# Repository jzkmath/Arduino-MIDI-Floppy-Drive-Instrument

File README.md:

# Arduino MIDI Floppy Drive Instrument

This is the design files for an Arduino Floppy-Drive controller that is MIDI Controlled.
It is a combination of the [MIDI Stepper Synth V1](https://github.com/jzkmath/Arduino-MIDI-Stepper-Motor-Instrument) and [Moppy Software](https://github.com/SammyIAm/Moppy2).

The core method for controlling the floppy drives is the use of a non-blocking delay. If you want to make a stepper motor play at a certain frequency, simply pulse the pin at that specified frequency. In this case however, the position of the drive head is important, so we simply need to track the position and reverse direction when that point is reached.

Refer to the schematic for pinouts. The header pins connect to the IDE connector of the floppy drive and maintain the ground reference.

Look at this pinout:

We need to connect "drive select" together (Pins 11 and 12) to enable the drive and then connect the Step and Direction to the Shield. 

### PINOUT:
12 - Drive Select (Enable)

11 - Drive Select Ground

18 - Direction

17 - Direction Ground

20 - Step

19 - Step Ground

## NOTE:
There is a two pin header (J14) that is the programming jumper. The jumper should be installed here and removed when the Arduino is being programmed. This is because the MIDI Rx line is also use to program the Arduino when its being flashed.

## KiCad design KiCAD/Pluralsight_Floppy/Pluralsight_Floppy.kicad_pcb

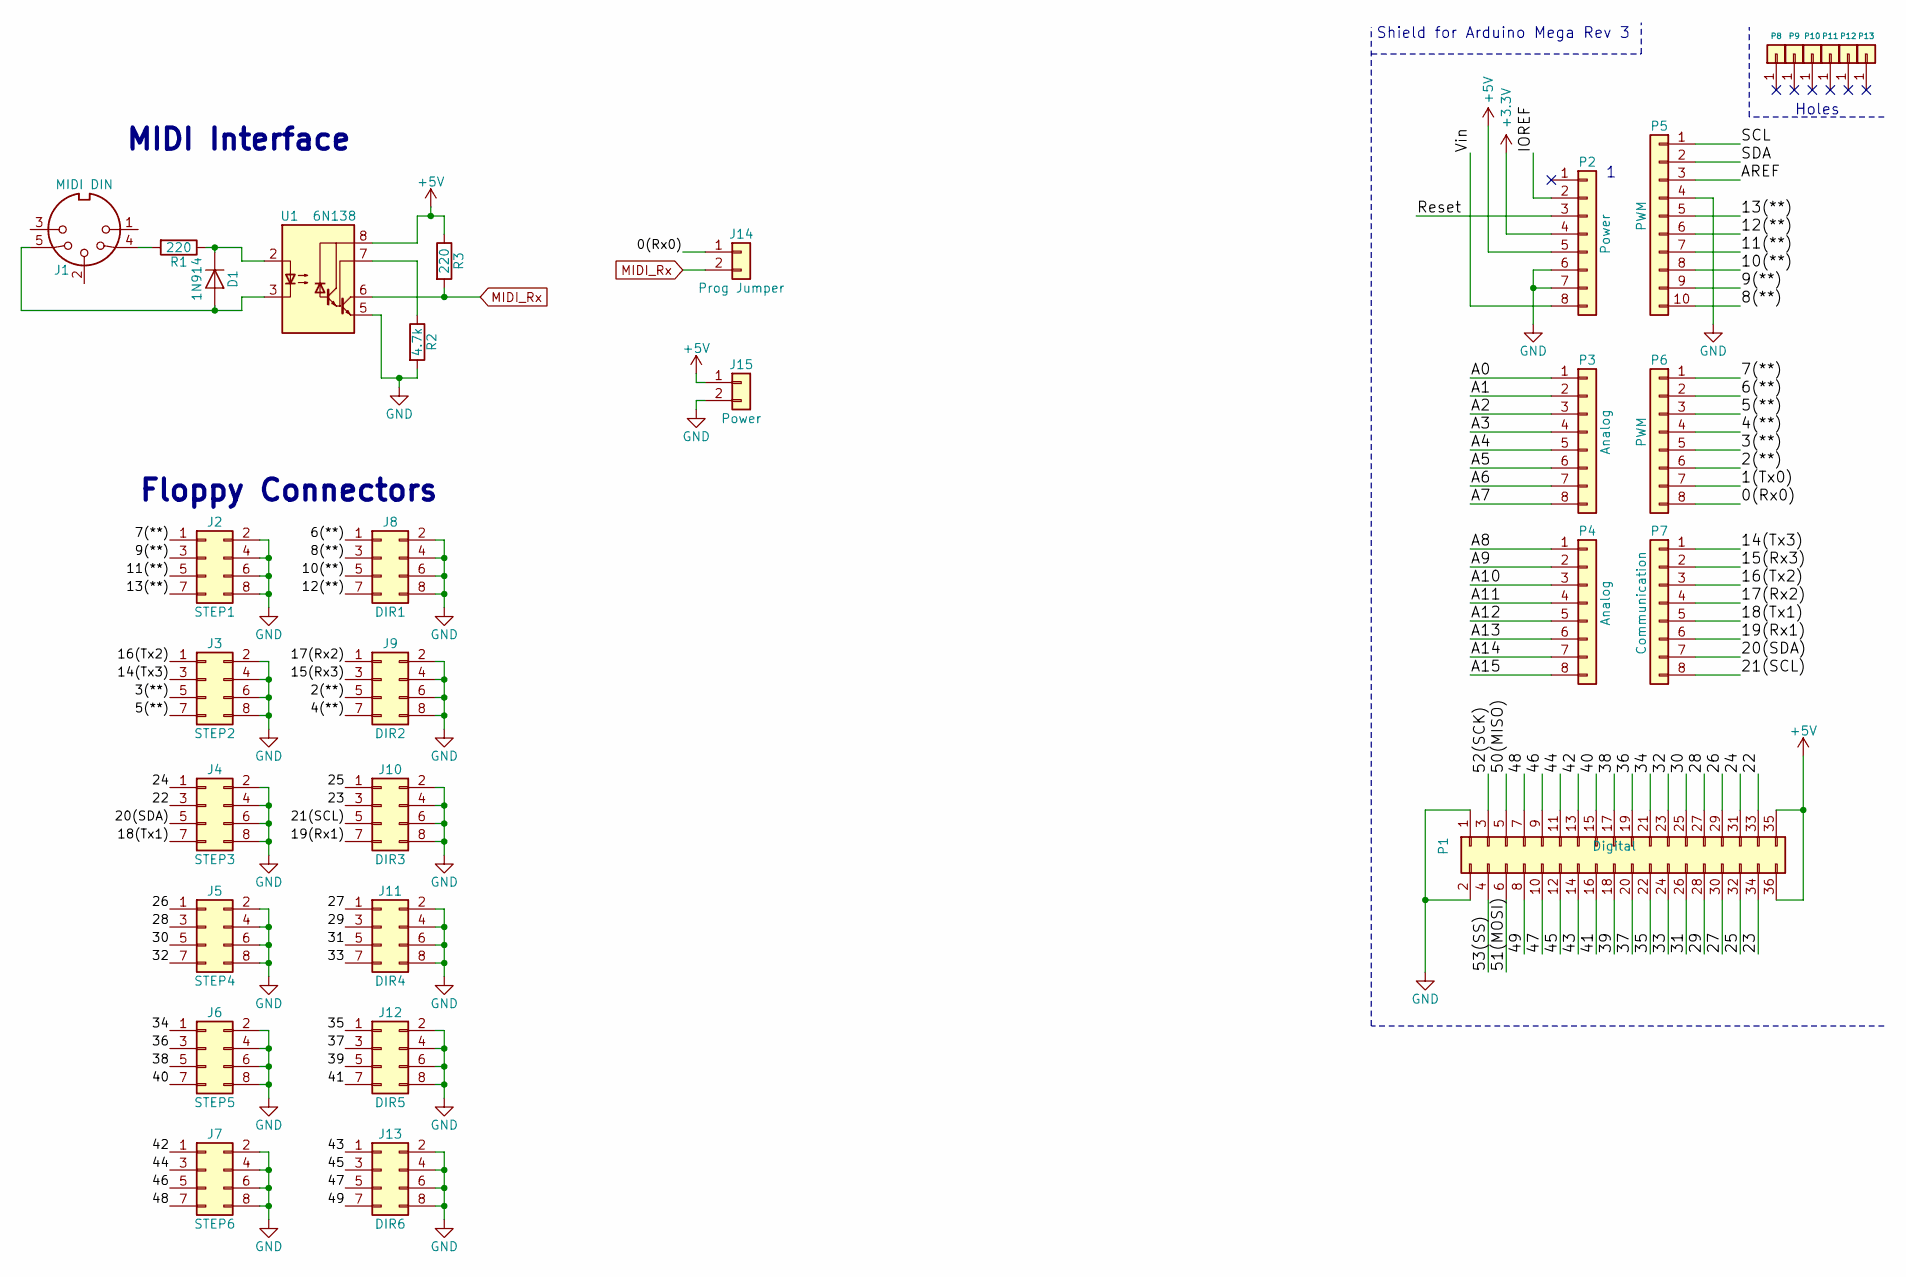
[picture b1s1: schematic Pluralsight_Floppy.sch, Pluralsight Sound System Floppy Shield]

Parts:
D1: 1N914; D_DO-15_P15.24mm_Horizontal
J1: MIDI DIN; SDS-50J
J2: STEP1; PinHeader_2x04_P2.54mm_Vertical_zigzag
J3: STEP2; PinHeader_2x04_P2.54mm_Vertical_zigzag
J4: STEP3; PinHeader_2x04_P2.54mm_Vertical_zigzag
J5: STEP4; PinHeader_2x04_P2.54mm_Vertical_zigzag
J6: STEP5; PinHeader_2x04_P2.54mm_Vertical_zigzag
J7: STEP6; PinHeader_2x04_P2.54mm_Vertical_zigzag
J8: DIR1; PinHeader_2x04_P2.54mm_Vertical_zigzag
J9: DIR2; PinHeader_2x04_P2.54mm_Vertical_zigzag
J10: DIR3; PinHeader_2x04_P2.54mm_Vertical_zigzag
J11: DIR4; PinHeader_2x04_P2.54mm_Vertical_zigzag
J12: DIR5; PinHeader_2x04_P2.54mm_Vertical_zigzag
J13: DIR6; PinHeader_2x04_P2.54mm_Vertical_zigzag
J14: Prog Jumper; PinHeader_1x02_P2.54mm_Vertical
J15: Power; 2_Pos_Screw_Term
P1: Digital; Socket_Strip_Arduino_2x18
P2: Power; Socket_Strip_Arduino_1x08
P3, P4: Analog; Socket_Strip_Arduino_1x08
P5: PWM; Socket_Strip_Arduino_1x10
P6: PWM; Socket_Strip_Arduino_1x08
P7: Communication; Socket_Strip_Arduino_1x08
P8, P9, P10, P11, P12, P13: CONN_01X01; Arduino_1pin
R1, R3: 220; R_Axial_DIN0207_L6.3mm_D2.5mm_P15.24mm_Horizontal
R2: 4.7k; R_Axial_DIN0207_L6.3mm_D2.5mm_P15.24mm_Horizontal
U1: 6N138; DIP-8_W7.62mm_LongPads

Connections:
+3V3: P2.4
+5V: J15.1, P1.35, P1.36, P2.5, R3.1, U1.8 (VCC)
/0(Rx0): J14.1, P6.8
/1(Tx0): P6.7
/2(**): J9.5, P6.6
/3(**): J3.5, P6.5
/4(**): J9.7, P6.4
/5(**): J3.7, P6.3
/6(**): J8.1, P6.2
/7(**): J2.1, P6.1
/8(**): J8.3, P5.10
/9(**): J2.3, P5.9
/10(**): J8.5, P5.8
/11(**): J2.5, P5.7
/12(**): J8.7, P5.6
/13(**): J2.7, P5.5
/14(Tx3): J3.3, P7.1
/15(Rx3): J9.3, P7.2
/16(Tx2): J3.1, P7.3
/17(Rx2): J9.1, P7.4
/18(Tx1): J4.7, P7.5
/19(Rx1): J10.7, P7.6
/20(SDA): J4.5, P7.7
/21(SCL): J10.5, P7.8
/22: J4.3, P1.33
/23: J10.3, P1.34
/24: J4.1, P1.31
/25: J10.1, P1.32
/26: J5.1, P1.29
/27: J11.1, P1.30
/28: J5.3, P1.27
/29: J11.3, P1.28
/30: J5.5, P1.25
/31: J11.5, P1.26
/32: J5.7, P1.23
/33: J11.7, P1.24
/34: J6.1, P1.21
/35: J12.1, P1.22
/36: J6.3, P1.19
/37: J12.3, P1.20
/38: J6.5, P1.17
/39: J12.5, P1.18
/40: J6.7, P1.15
/41: J12.7, P1.16
/42: J7.1, P1.13
/43: J13.1, P1.14
/44: J7.3, P1.11
/45: J13.3, P1.12
/46: J7.5, P1.9
/47: J13.5, P1.10
/48: J7.7, P1.7
/49: J13.7, P1.8
/50(MISO): P1.5
/51(MOSI): P1.6
/52(SCK): P1.3
/53(SS): P1.4
/A0: P3.1
/A1: P3.2
/A2: P3.3
/A3: P3.4
/A4: P3.5
/A5: P3.6
/A6: P3.7
/A7: P3.8
/A8: P4.1
/A9: P4.2
/A10: P4.3
/A11: P4.4
/A12: P4.5
/A13: P4.6
/A14: P4.7
/A15: P4.8
/AREF: P5.3
/IOREF: P2.2
/Reset: P2.3
/SCL: P5.1
/SDA: P5.2
/Vin: P2.8
GND: J2.2, J2.4, J2.6, J2.8, J3.2, J3.4, J3.6, J3.8, J4.2, J4.4, J4.6, J4.8, J5.2, J5.4, J5.6, J5.8, J6.2, J6.4, J6.6, J6.8, J7.2, J7.4, J7.6, J7.8, J8.2, J8.4, J8.6, J8.8, J9.2, J9.4, J9.6, J9.8, J10.2, J10.4, J10.6, J10.8, J11.2, J11.4, J11.6, J11.8, J12.2, J12.4, J12.6, J12.8, J13.2, J13.4, J13.6, J13.8, J15.2, P1.1, P1.2, P2.6, P2.7, P5.4, R2.2, U1.5 (GND)
MIDI_Rx: J14.2, R3.2, U1.6 (VO2)
unnamed: D1.1 (K), R1.1, U1.2 (C1)
unnamed: D1.2 (A), J1.5, U1.3 (C2)
unnamed: J1.4, R1.2
unnamed: R2.1, U1.7 (VO1)

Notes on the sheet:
Shield for Arduino Mega Rev 3
Holes
MIDI Interface
Floppy Connectors

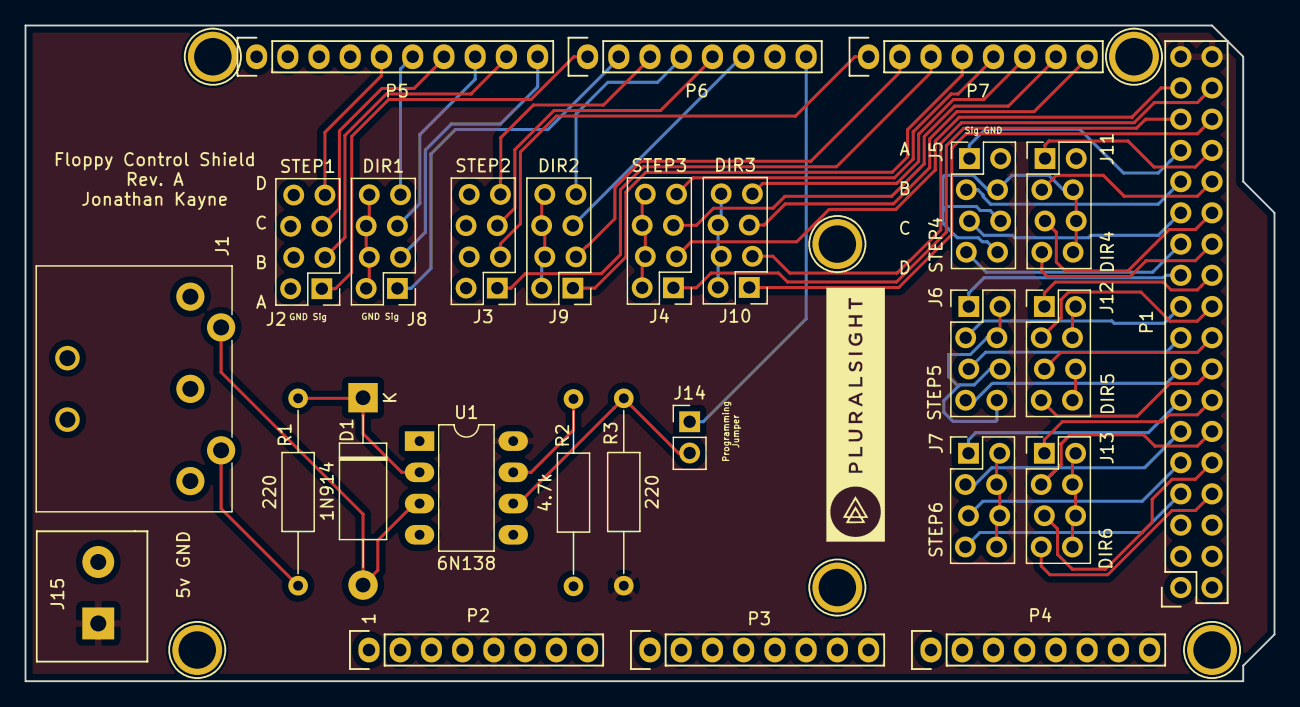
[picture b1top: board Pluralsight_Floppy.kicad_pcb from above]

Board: 2 copper layers, 101.6 x 53.3 mm, 33 parts (0 on the bottom side), 56 nets.

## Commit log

2019-04-26 Added KiCAD files
2019-04-26 Added Arduino Code
2019-05-24 mocuLUFA hex file
